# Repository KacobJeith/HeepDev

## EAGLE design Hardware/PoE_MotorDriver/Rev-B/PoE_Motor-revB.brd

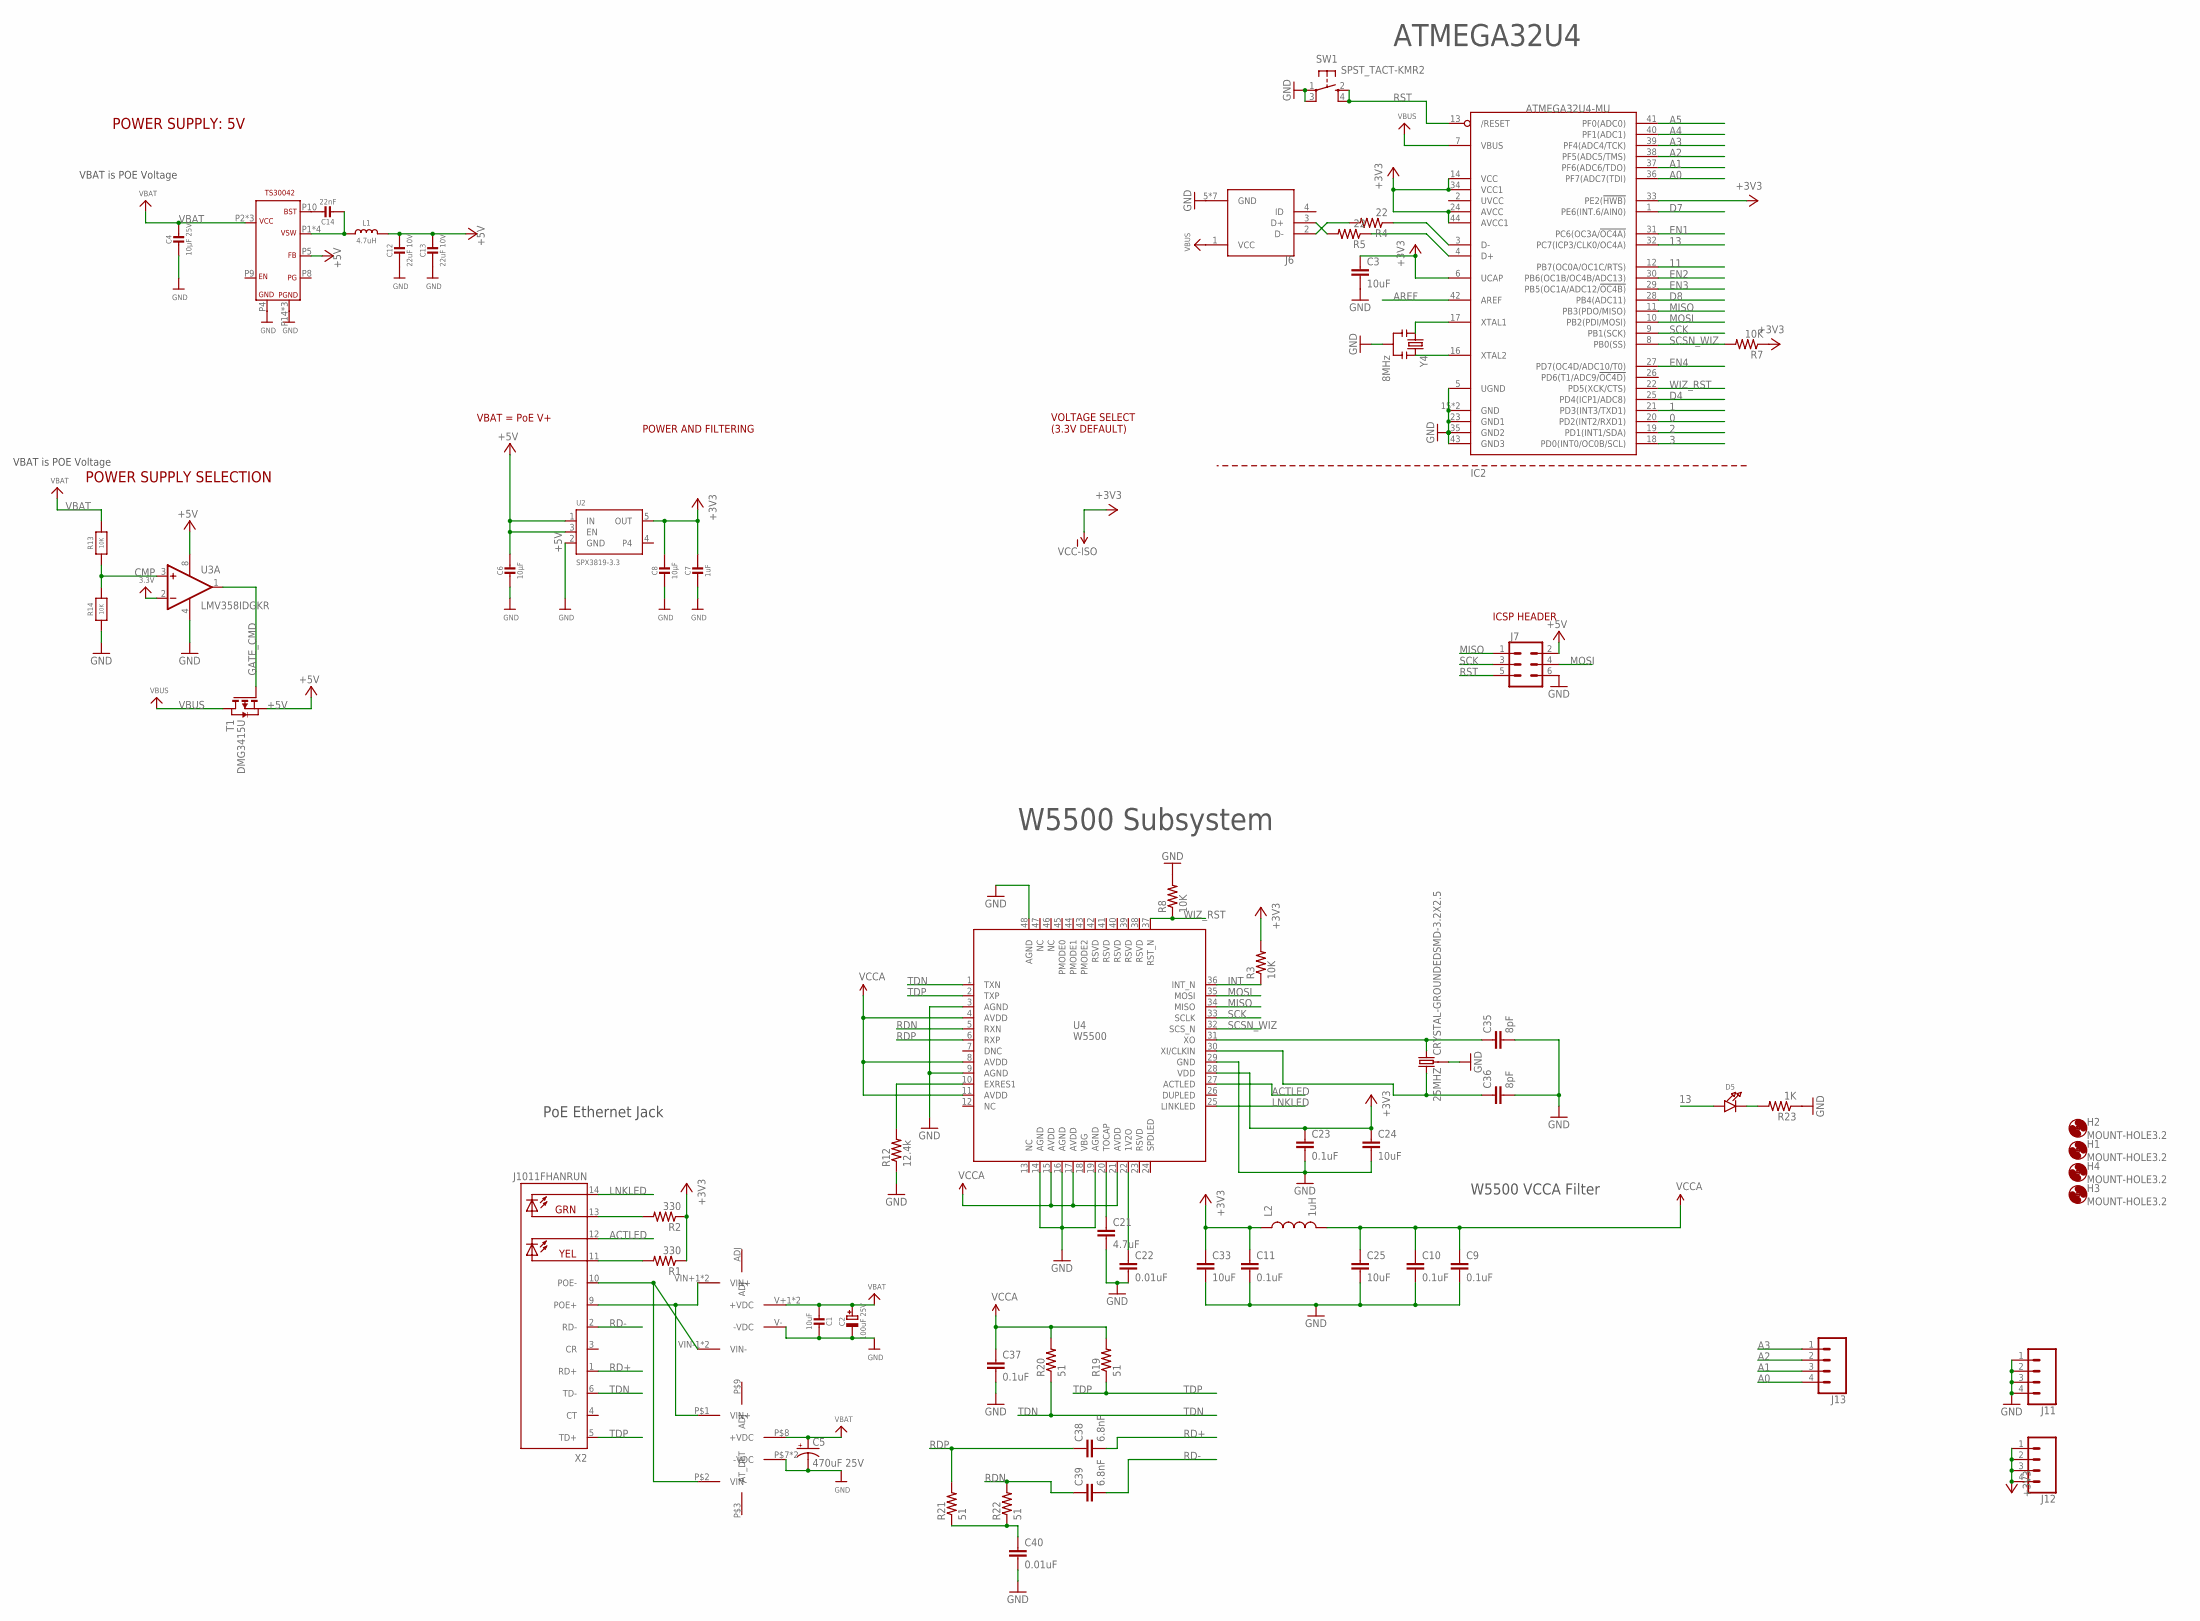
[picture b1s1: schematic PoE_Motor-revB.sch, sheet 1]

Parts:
25MHZ: CRYSTAL-GROUNDEDSMD-3.2X2.5; CRYSTAL-SMD-3.2X2.5MM
C1: 10uF; _0805MP
C2: 100uF 25V; PANASONIC_D
C3, C24, C25, C33: 10uF; 0603-CAP
C4: 10µF 25V; 0603-MINI
C5: 470uF 25V; PANASONIC_G
C6, C8: 10µF; 0603-MINI
C7: 1uF; 0603-MINI
C9, C10, C11, C23, C37: 0.1uF; 0603-CAP
C12, C13: 22uF 10V; 0603-MINI
C14: 22nF; 0603-MINI
C21: 4.7uF; 0603-CAP
C22, C40: 0.01uF; 0603-CAP
C35, C36: 8pF; 0603-CAP
C38, C39: 6.8nF; 0603-CAP
D5: LED0805_NOOUTLINE; CHIPLED_0805_NOOUTLINE
H1, H2, H3, H4: MOUNT-HOLE3.2; 3,2
IC2: ATMEGA32U4-MU; TQFN44_7MM
J6: 10103594-0001LF; FCI_10103594-0001LF
J7: CONN_03X2NO_SILK; 2X3-NS
J11, J12: CONN_04; 1X04
J13: CONN_041X04_NO_SILK; 1X04_NO_SILK
L1: 4.7uH; INDUCTOR_5X5MM_TDK_VLC5045
L2: 1uH; 0603
R1, R2: 330; 0603-RES
R3, R7, R8: 10K; 0603-RES
R4, R5: 22; 0603-RES
R12: 12.4k; 0603-RES
R13, R14: 10K; 0603-NO
R19, R20, R21, R22: 51; 0603-RES
R23: 1K; 0603-RES
SW1: SPST_TACT-KMR2; KMR2
T1: DMG3415U; SOT-23
U2: SPX3819-3.3; SOT23-5
U3: LMV358IDGKR; MSOP08
U4: W5500
U$1: SILVERTEL_POEMICRO; AG9900
U$16: AG5200AG5300; AG5300
U$19: BUCK_CONVERTER; QFN-16
X2: J1011FHANRUN; HANRUN_POE
Y4: 8MHz; RESONATOR-SMD

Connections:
0: IC2.20 (PD2(INT2/RXD1))
1: IC2.21 (PD3(INT3/TXD1))
2: IC2.19 (PD1(INT1/SDA))
3: IC2.18 (PD0(INT0/OC0B/SCL))
11: IC2.12 (PB7(OC0A/OC1C/RTS))
13: D5.A, IC2.32 (PC7(ICP3/CLK0/OC4A))
+3V3: C3.1, C7.1, C8.1, C11.1, C23.1, C24.1, C33.1, IC2.6 (UCAP), IC2.14 (VCC), IC2.24 (AVCC), IC2.33 (PE2(!HWB)), IC2.34 (VCC1), IC2.44 (AVCC1), J12.1, J12.2, J12.3, J12.4, L2.1, R1.1, R2.1, R3.2, R7.1, U2.5 (OUT), U3.2 (-IN), U4.28 (VDD)
+5V: C6.1, C12.1, C13.1, J7.2, L1.P$2 (2), T1.2 (S), U2.1 (IN), U2.3 (EN), U3.8 (V+), U$19.P5 (FB)
A0: IC2.36 (PF7(ADC7(TDI)), J13.4
A1: IC2.37 (PF6(ADC6/TDO)), J13.3
A2: IC2.38 (PF5(ADC5/TMS)), J13.2
A3: IC2.39 (PF4(ADC4/TCK)), J13.1
A4: IC2.40 (PF1(ADC1))
A5: IC2.41 (PF0(ADC0))
ACTLED: U4.27 (ACTLED), X2.12 (YEL-C)
AREF: IC2.42 (AREF)
CMP: R13.1, R14.2, U3.3 (+IN)
D4: IC2.25 (PD4(ICP1/ADC8))
D7: IC2.1 (PE6(INT.6/AIN0))
D8: IC2.28 (PB4(ADC11))
D+: IC2.4 (D+), R5.1
D-: IC2.3 (D-), R4.1
EN1: IC2.31 (PC6(OC3A/!OC4A)); also elsewhere on the board
EN2: IC2.30 (PB6(OC1B/OC4B/ADC13)); also elsewhere on the board
EN3: IC2.29 (PB5(OC1A/ADC12/!OC4B)); also elsewhere on the board
EN4: IC2.27 (PD7(OC4D/ADC10/T0)); also elsewhere on the board
GATE_CMD: T1.3 (G), U3.1 (OUT)
GND: 25MHZ.2 (3), 25MHZ.4 (3), C1.1, C2.-, C3.2, C4.2, C5.-, C6.2, C7.2, C8.2, C9.2, C10.2, C11.2, C12.2, C13.2, C21.2, C22.2, C23.2, C24.2, C25.2, C33.2, C35.2, C36.2, C37.2, C40.2, IC2.5 (UGND), IC2.15 (GND), IC2.23 (GND1), IC2.35 (GND2), IC2.43 (GND3), IC2.THERMAL (GND), J6.5 (GND), J6.P1 (GND), J6.P2 (GND), J6.P3 (GND), J6.P4 (GND), J6.P5 (GND), J6.P6 (GND), J7.6, J11.1, J11.2, J11.3, J11.4, R8.2, R12.1, R14.1, R23.1, SW1.1, SW1.3 (P1), U2.2 (GND), U3.4 (V-), U4.3 (AGND), U4.9 (AGND), U4.14 (AGND), U4.16 (AGND), U4.19 (AGND), U4.29 (GND), U4.48 (AGND), U$1.V- (-VDC), U$16.P$7 (-VDC), U$16.P$10 (-VDC), U$19.P4 (GND), U$19.P14 (PGND), U$19.P15 (PGND), U$19.PAD (PGND), Y4.2; also elsewhere on the board
INT: R3.1, U4.36 (INT_N)
LNKLED: U4.25 (LINKLED), X2.14 (GRN-C)
MISO: IC2.11 (PB3(PDO/MISO)), J7.1, U4.34 (MISO)
MOSI: IC2.10 (PB2(PDI/MOSI)), J7.4, U4.35 (MOSI)
unnamed: U$1.VIN-1 (VIN-), U$1.VIN-2 (VIN-), U$16.P$2 (VIN-), X2.10 (POE-)
unnamed: U$1.VIN+1 (VIN+), U$1.VIN+2 (VIN+), U$16.P$1 (VIN+), X2.9 (POE+)
unnamed: R2.2, X2.13 (GRN-A)
unnamed: R1.2, X2.11 (YEL-A)
unnamed: J6.3 (D+), R5.2
unnamed: D5.C, R23.2
unnamed: IC2.16 (XTAL2), Y4.3
unnamed: IC2.17 (XTAL1), Y4.1
unnamed: J6.2 (D-), R4.2
unnamed: C14.1, U$19.P10 (BST)
unnamed: C14.2, L1.P$1 (1), U$19.P1 (VSW), U$19.P12 (VSW), U$19.P13 (VSW), U$19.P16 (VSW)
unnamed: C21.1, U4.20 (TOCAP)
unnamed: C22.1, U4.22 (1V2O)
unnamed: R12.2, U4.10 (EXRES1)
unnamed: C40.1, R21.1, R22.1
unnamed: 25MHZ.3 (2), C35.1, U4.31 (XO)
unnamed: 25MHZ.1, C36.1, U4.30 (XI/CLKIN)
RD+: C38.2, X2.1 (RD+)
RD-: C39.2, X2.2 (RD-)
RDN: C39.1, R22.2, U4.5 (RXN)
RDP: C38.1, R21.2, U4.6 (RXP)
RST: IC2.13 (/RESET), J7.5, SW1.2 (S), SW1.4 (S1)
SCK: IC2.9 (PB1(SCK)), J7.3, U4.33 (SCLK)
SCSN_WIZ: IC2.8 (PB0(SS)), R7.2, U4.32 (SCS_N)
TDN: R20.1, U4.1 (TXN), X2.6 (TD-)
TDP: R19.1, U4.2 (TXP), X2.5 (TD+)
VBAT: C1.2, C2.+, C4.1, C5.+, R13.2, U$1.V+1 (+VDC), U$1.V+2 (+VDC), U$16.P$8 (+VDC), U$19.P2 (VCC), U$19.P3 (VCC), U$19.P11 (VCC); also elsewhere on the board
VBUS: IC2.7 (VBUS), J6.1 (VCC), T1.1 (D)
VCCA: C9.1, C10.1, C25.1, C37.1, L2.2, R19.2, R20.2, U4.4 (AVDD), U4.8 (AVDD), U4.11 (AVDD), U4.15 (AVDD), U4.17 (AVDD), U4.21 (AVDD)
WIZ_RST: IC2.22 (PD5(XCK/CTS)), R8.1, U4.37 (RST_N)

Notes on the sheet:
W5500 Subsystem
W5500 VCCA Filter
POWER AND FILTERING
VBAT = PoE V+
VOLTAGE SELECT (3.3V DEFAULT)
PoE Ethernet Jack
ATMEGA32U4
ICSP HEADER
POWER SUPPLY: 5V
POWER SUPPLY SELECTION
VBAT is POE Voltage

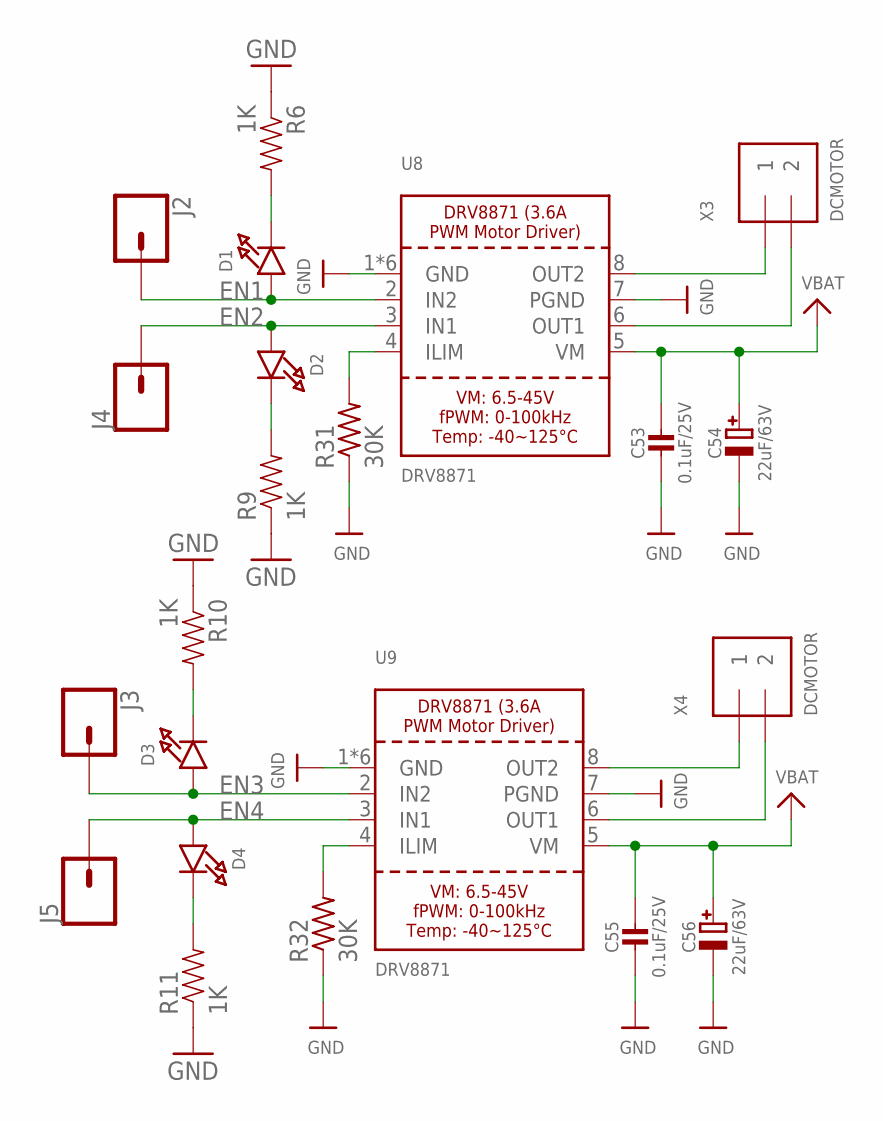
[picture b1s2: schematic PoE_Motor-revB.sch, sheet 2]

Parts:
C53, C55: 0.1uF/25V; 0603-NO
C54, C56: 22uF/63V; PANASONIC_D
D1, D2, D3, D4: LED0805_NOOUTLINE; CHIPLED_0805_NOOUTLINE
J2, J3, J4, J5: CONN_01; 1X01
R6, R9, R10, R11: 1K; 0603-RES
R31, R32: 30K; 0805-THM
U8, U9: DRV8871; HSOP8
X3, X4: DCMOTOR; TERMBLOCK_1X2-3.5MM

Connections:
EN1: D1.A, J2.1, U8.2 (IN2); also elsewhere on the board
EN2: D2.A, J4.1, U8.3 (IN1); also elsewhere on the board
EN3: D3.A, J3.1, U9.2 (IN2); also elsewhere on the board
EN4: D4.A, J5.1, U9.3 (IN1); also elsewhere on the board
GND: C53.2, C54.-, C55.2, C56.-, R6.1, R9.1, R10.1, R11.1, R31.1, R32.1, U8.1 (GND), U8.7 (PGND), U8.GND, U8.P$1 (GND), U8.P$2 (GND), U8.P$3 (GND), U8.P$4 (GND), U9.1 (GND), U9.7 (PGND), U9.GND, U9.P$1 (GND), U9.P$2 (GND), U9.P$3 (GND), U9.P$4 (GND); also elsewhere on the board
unnamed: D1.C, R6.2
unnamed: D2.C, R9.2
unnamed: D3.C, R10.2
unnamed: D4.C, R11.2
unnamed: R31.2, U8.4 (ILIM)
unnamed: R32.2, U9.4 (ILIM)
OUT1: U8.6 (OUT1), X3.2
OUT2: U8.8 (OUT2), X3.1
OUT3: U9.8 (OUT2), X4.1
OUT4: U9.6 (OUT1), X4.2
VBAT: C53.1, C54.+, C55.1, C56.+, U8.5 (VM), U9.5 (VM); also elsewhere on the board

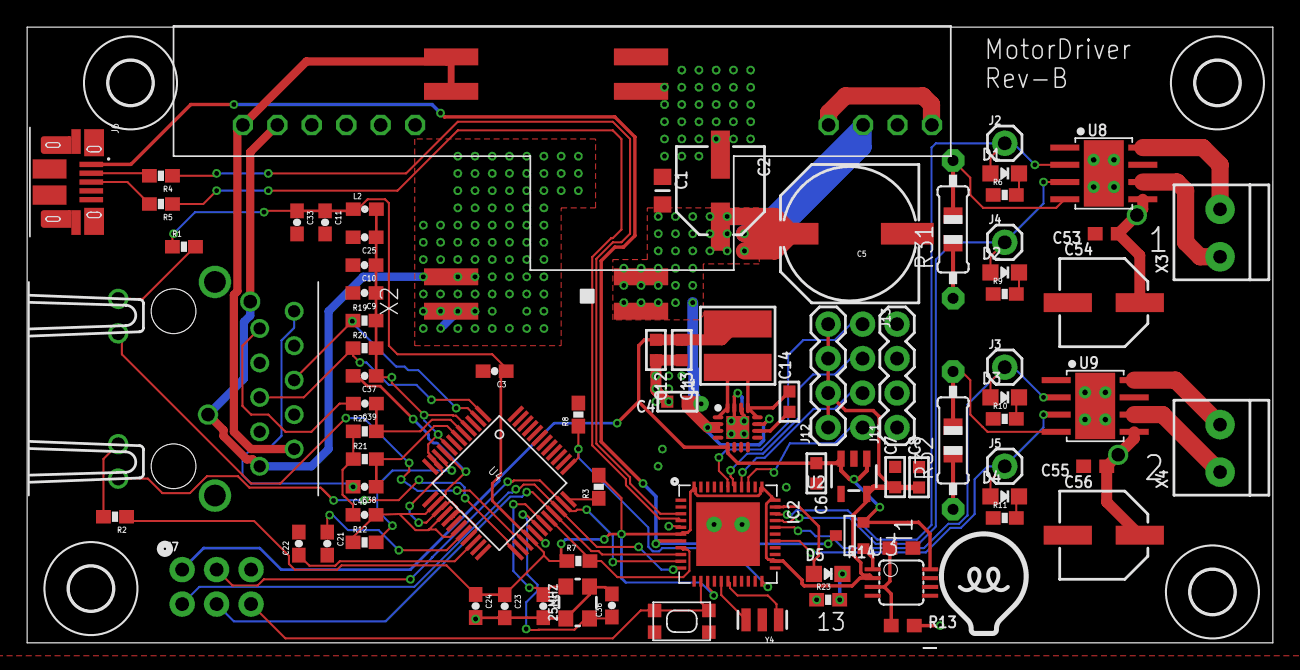
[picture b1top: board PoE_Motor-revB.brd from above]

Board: 2 copper layers, 91.8 x 45.4 mm, 88 parts (0 on the bottom side), 61 nets.

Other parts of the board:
U$15: HEEPLOGOSMALL

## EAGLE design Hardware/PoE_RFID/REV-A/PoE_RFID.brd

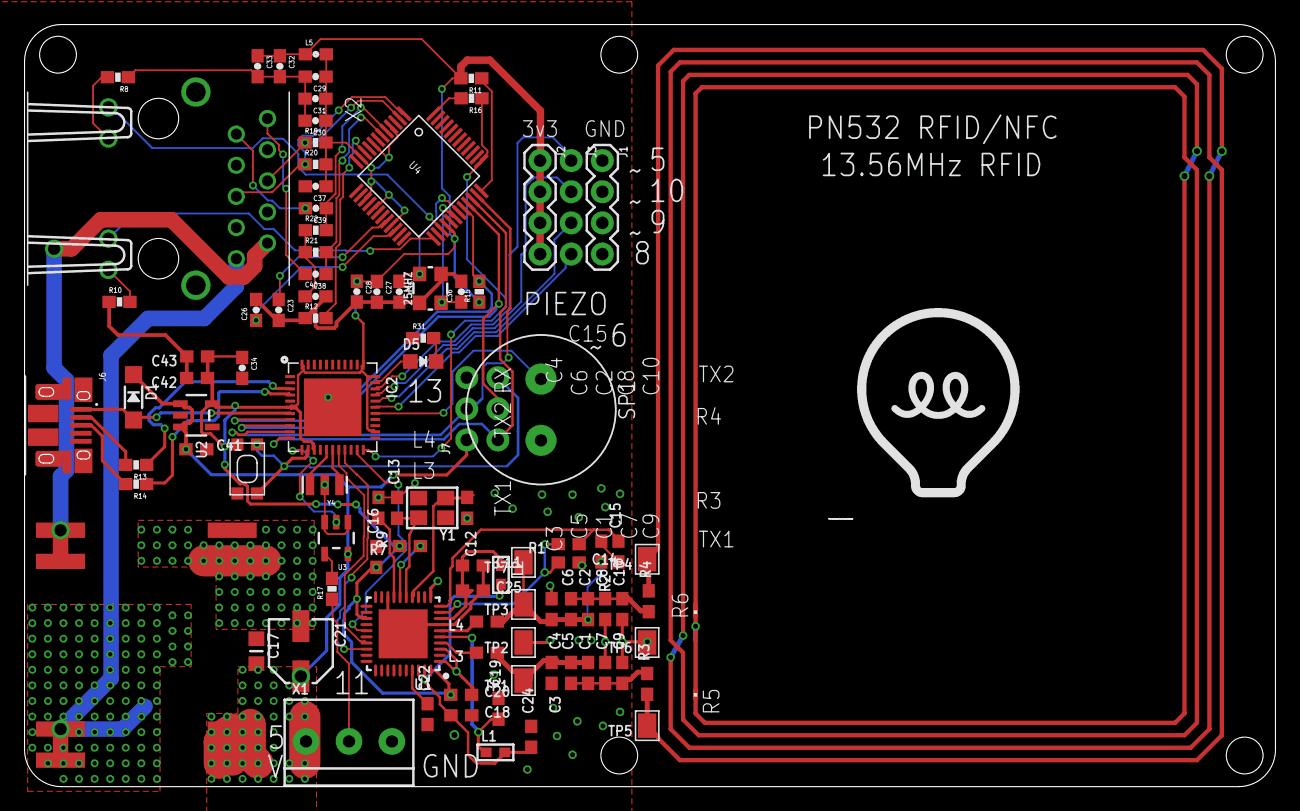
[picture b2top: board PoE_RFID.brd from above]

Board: 2 copper layers, 102.0 x 62.1 mm, 98 parts (0 on the bottom side), 68 nets.

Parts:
25MHZ: CRYSTAL-GROUNDEDSMD-3.2X2.5; CRYSTAL-SMD-3.2X2.5MM
C1, C2, C12, C13: 22pF; 0603-NO
C3, C4: 220pF; 0603-NO
C5, C6, C9, C10: NC; 0603-NO
C7, C8: 100pF; 0603-NO
C11, C14, C16, C20, C24: 0.1µF; 0603-NO
C15: 1000pF; 0603-NO
C17: 10uF; _0805MP
C18, C19, C22, C25, C41, C43: 10µF; 0603-NO
C21: 100uF; PANASONIC_C
C23: 4.7uF; 0603-CAP
C26, C40: 0.01uF; 0603-CAP
C27, C30, C31, C32, C37: 0.1uF; 0603-CAP
C28, C29, C33, C34: 10uF; 0603-CAP
C35, C36: 8pF; 0603-CAP
C38, C39: 6.8nF; 0603-CAP
C42: 1uF; 0603-NO
D1: SOD-123
D5: CHIPLED_0805_NOOUTLINE
IC2: ATMEGA32U4-MU; TQFN44_7MM
J1, J2: 1X04
J3: 1X04_NO_SILK
J6: 10103594-0001LF; FCI_10103594-0001LF
J7: 2X3-NS
L1, L2: FERRITE; _0603
L3, L4: 560nH; 0603-NO
L5: 1uH; 0603
R1: 1.0K; 0603-NO
R2: 1.69K; 0603-NO
R3, R4: 1.5; 0603-NO
R5, R6: NC; R0201
R7, R9: 10K; 0603-NO
R8, R10: 330; 0603-RES
R11, R15, R16: 10K; 0603-RES
R12: 12.4k; 0603-RES
R13, R14: 22; 0603-RES
R17: 100; 0603-RES
R19, R20, R21, R22: 51; 0603-RES
R31: 1K; 0603-RES
SP1: SPEAKER/PS12; PS12
SW1: SPST_TACT-KMR2; KMR2
TP1: TX1_POST; PAD-1.5X2.0
TP2, TP6: TGND; PAD-1.5X2.0
TP3: TX2_POST; PAD-1.5X2.0
TP4: TX2_PRE; PAD-1.5X2.0
TP5: TX1_PRE; PAD-1.5X2.0
TP7: RX; PAD-1.5X2.0
U1: PN532; HVQFN40-6X6
U2: SPX3819-3.3; SOT23-5
U3: 74AHC1G125; SOT23-5
U4: W5500
U$1: SILVERTEL_POEMICRO; AG9900
U$19: HEEPLOGO
X1: TERMBLOCK_1X3-3.5MM
X2: J1011FHANRUN; HANRUN_POE
Y1: 27.12MHz; CRYSTAL_3.2X2.5
Y4: 8MHz; RESONATOR-SMD

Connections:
5_PWM: IC2.31, J3.1
9_PWM: IC2.29, J3.3
10_PWM: IC2.30, J3.2
13: D5.A, IC2.32
+3V3: C16.1, C20.1, C27.1, C28.1, C32.1, C33.1, C34.1, C42.1, C43.1, IC2.6, IC2.14, IC2.24, IC2.33, IC2.34, IC2.44, J2.1, J2.2, J2.3, J2.4, L5.1, R7.2, R11.2, R15.1, U1.23, U1.40, U2.5, U4.28
+5V: C17.2, C21.+, C41.1, D1.C, J7.2, U2.1, U2.3, U3.5, U$1.V+1, U$1.V+2, X1.3
ACTLED: U4.27, X2.11
D8: IC2.28, J3.4
D+: IC2.4, R14.1
D-: IC2.3, R13.1
EN3: IC2.27, SP1.P$1
GND: 25MHZ.2, 25MHZ.4, C3.2, C4.1, C7.2, C8.1, C9.2, C10.1, C11.2, C12.2, C13.2, C14.2, C16.2, C17.1, C18.2, C19.2, C20.2, C21.-, C22.1, C23.2, C24.2, C25.2, C26.2, C27.2, C28.2, C29.2, C30.2, C31.2, C32.2, C33.2, C34.2, C35.2, C36.2, C37.2, C40.2, C41.2, C42.2, C43.2, IC2.5, IC2.15, IC2.23, IC2.35, IC2.43, IC2.THERMAL, J1.1, J1.2, J1.3, J1.4, J6.5, J6.P1, J6.P2, J6.P3, J6.P4, J6.P5, J6.P6, J7.6, R5.2, R6.1, R8.1, R9.1, R10.1, R12.1, R16.2, R31.1, SP1.P$2, SW1.1, SW1.3, TP2.P$1, TP6.P$1, U1.1, U1.3, U1.7, U1.11, U1.18, U1.TP, U2.2, U3.1, U3.3, U4.3, U4.9, U4.14, U4.16, U4.19, U4.29, U4.48, U$1.V-, X1.1, Y4.2
INT: R11.1, U4.36
IRQ: IC2.21, U1.25
LNKLED: U4.25, X2.13
MISO: IC2.11, J7.1, U4.34
MOSI: IC2.10, J7.4, U4.35
MOSI/SDA/TX: IC2.19, U1.28
unnamed: L3.2, U1.4
unnamed: L4.2, U1.6
unnamed: C1.2, C3.1, C5.2, L3.1, TP1.P$1
unnamed: R3.1, R6.2, TP5.P$1
unnamed: R4.2, R5.1, TP4.P$1
unnamed: U$1.VIN-1, U$1.VIN-2, X2.10
unnamed: C12.1, U1.14, Y1.1
unnamed: C13.1, U1.15, Y1.2
unnamed: C15.1, R2.1
unnamed: C14.1, R1.2, U1.9
unnamed: C15.2, R1.1, U1.10
unnamed: C2.1, C4.2, C6.1, L4.1, R2.2, TP3.P$1, TP7.P$1
unnamed: C11.1, C25.1, L2.1, U1.8
unnamed: C19.1, L1.1, U1.5
unnamed: U$1.VIN+1, U$1.VIN+2, X2.9
unnamed: C26.1, U4.22
unnamed: IC2.16, Y4.3
unnamed: C23.1, U4.20
unnamed: R17.2, U3.4
unnamed: R12.2, U4.10
unnamed: IC2.17, Y4.1
unnamed: J6.3, R14.2
unnamed: C40.1, R21.1, R22.1
unnamed: J6.2, R13.2
unnamed: 25MHZ.3, C35.1, U4.31
unnamed: 25MHZ.1, C36.1, U4.30
unnamed: R10.2, X2.14
unnamed: R8.2, X2.12
unnamed: D5.C, R31.2
unnamed: C22.2, U1.37
NEO_3V: IC2.12, U3.2
NEO_5V: R17.1, X1.2
NSS/SCL/RX: IC2.18, U1.27
RD+: C38.2, X2.1
RD-: C39.2, X2.2
RDN: C39.1, R22.2, U4.5
RDP: C38.1, R21.2, U4.6
RST: IC2.13, J7.5, SW1.2, SW1.4
SCK: IC2.9, J7.3, U4.33
SCSN_WIZ: IC2.8, R15.2, U4.32
SEL0: R7.1, U1.16
SEL1: R9.2, U1.17
TDN: R20.1, U4.1, X2.6
TDP: R19.1, U4.2, X2.5
TX1_ANTENNA: C1.1, C5.1, C7.1, C9.1, R3.2
TX2_ANTENNA: C2.2, C6.2, C8.2, C10.2, R4.1
VBUS: D1.A, IC2.7, J6.1
VCC: C18.1, C24.1, L1.2, L2.2, U1.39
VCCA: C29.1, C30.1, C31.1, C37.1, L5.2, R19.2, R20.2, U4.4, U4.8, U4.11, U4.15, U4.17, U4.21
WIZ_RST: IC2.22, R16.1, U4.37

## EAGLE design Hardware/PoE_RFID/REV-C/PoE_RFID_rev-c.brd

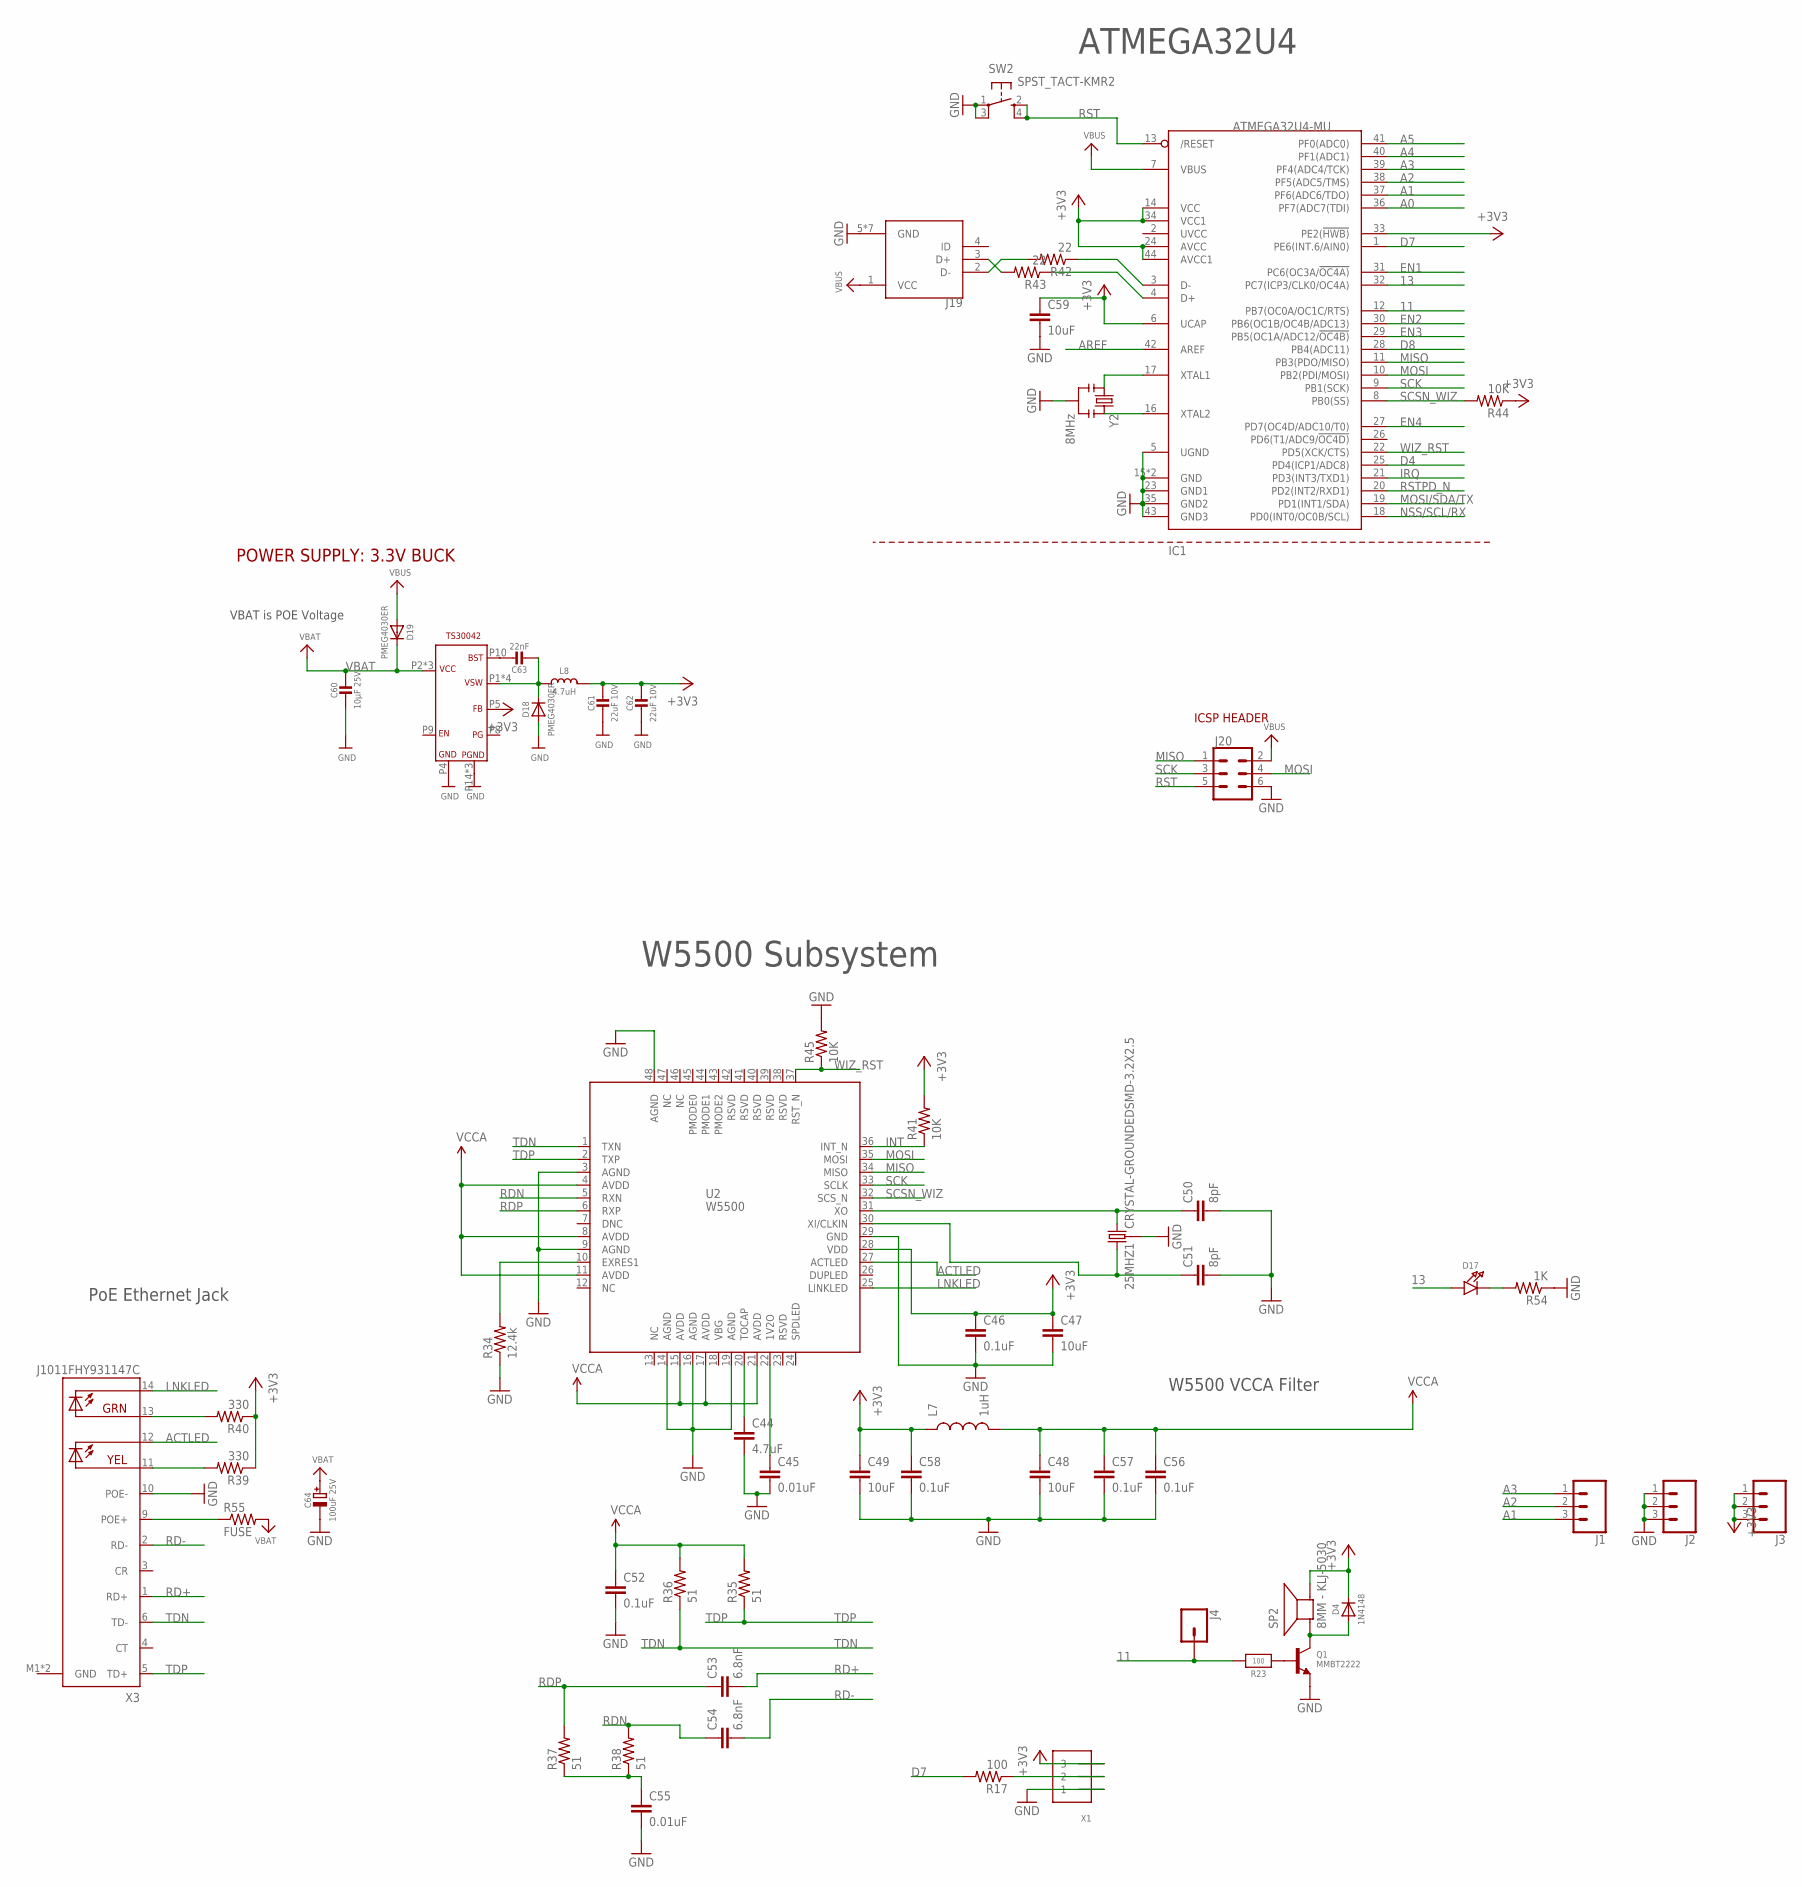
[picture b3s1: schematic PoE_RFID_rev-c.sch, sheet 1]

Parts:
25MHZ1: CRYSTAL-GROUNDEDSMD-3.2X2.5; CRYSTAL-SMD-3.2X2.5MM
C44: 4.7uF; 0603-CAP
C45, C55: 0.01uF; 0603-CAP
C46, C52, C56, C57, C58: 0.1uF; 0603-CAP
C47, C48, C49, C59: 10uF; 0603-CAP
C50, C51: 8pF; 0603-CAP
C53, C54: 6.8nF; 0603-CAP
C60: 10µF 25V; 0603-MINI
C61, C62: 22uF 10V; 0603-MINI
C63: 22nF; 0603-MINI
C64: 100uF 25V; PANASONIC_D
D4: 1N4148; SOD-323
D17: LED0805_NOOUTLINE; CHIPLED_0805_NOOUTLINE
D18, D19: PMEG4030ER; SOD-123
IC1: ATMEGA32U4-MU; TQFN44_7MM
J1: CONN_031X03_NO_SILK; 1X03_NO_SILK
J2, J3: CONN_03; 1X03
J4: CONN_01; 1X01
J19: 10103594-0001LF; FCI_10103594-0001LF
J20: CONN_03X2NO_SILK; 2X3-NS
L7: 1uH; 0603
L8: 4.7uH; INDUCTOR_5X5MM_TDK_VLC5045
Q1: MMBT2222; SOT23-WIDE
R17: 100; 0603-RES
R23: 100; 0603-NO@1
R34: 12.4k; 0603-RES
R35, R36, R37, R38: 51; 0603-RES
R39, R40: 330; 0603-RES
R41, R44, R45: 10K; 0603-RES
R42, R43: 22; 0603-RES
R54: 1K; 0603-RES
R55: FUSE; 0603-RES
SP2: 8MM - KLJ-5030; BUZZER_SMT_5MM
SW2: SPST_TACT-KMR2; KMR2
U2: W5500
U$55: BUCK_CONVERTER; QFN-16
X1: TERMBLOCK_1X3; TERMBLOCK_1X3-3.5MM
X3: J1011FHY931147C; HANRUN_POE
Y2: 8MHz; RESONATOR-SMD

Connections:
11: IC1.12 (PB7(OC0A/OC1C/RTS)), J4.1, R23.2
13: D17.A, IC1.32 (PC7(ICP3/CLK0/OC4A))
+3V3: C46.1, C47.1, C49.1, C58.1, C59.1, C61.1, C62.1, D4.C, IC1.6 (UCAP), IC1.14 (VCC), IC1.24 (AVCC), IC1.33 (PE2(!HWB)), IC1.34 (VCC1), IC1.44 (AVCC1), J3.1, J3.2, J3.3, L7.1, L8.P$2 (2), R39.1, R40.1, R41.2, R44.1, SP2.-, U2.28 (VDD), U$55.P5 (FB), X1.3; also elsewhere on the board
A0: IC1.36 (PF7(ADC7(TDI))
A1: IC1.37 (PF6(ADC6/TDO)), J1.3
A2: IC1.38 (PF5(ADC5/TMS)), J1.2
A3: IC1.39 (PF4(ADC4/TCK)), J1.1
A4: IC1.40 (PF1(ADC1))
A5: IC1.41 (PF0(ADC0))
ACTLED: U2.27 (ACTLED), X3.12 (YEL-C)
AREF: IC1.42 (AREF)
D4: IC1.25 (PD4(ICP1/ADC8))
D7: IC1.1 (PE6(INT.6/AIN0)), R17.2
D8: IC1.28 (PB4(ADC11))
D+1: IC1.4 (D+), R43.1
D-1: IC1.3 (D-), R42.1
EN1: IC1.31 (PC6(OC3A/!OC4A))
EN2: IC1.30 (PB6(OC1B/OC4B/ADC13))
EN3: IC1.29 (PB5(OC1A/ADC12/!OC4B))
EN4: IC1.27 (PD7(OC4D/ADC10/T0))
GND: 25MHZ1.2 (3), 25MHZ1.4 (3), C44.2, C45.2, C46.2, C47.2, C48.2, C49.2, C50.2, C51.2, C52.2, C55.2, C56.2, C57.2, C58.2, C59.2, C60.2, C61.2, C62.2, C64.-, D18.A, IC1.5 (UGND), IC1.15 (GND), IC1.23 (GND1), IC1.35 (GND2), IC1.43 (GND3), IC1.THERMAL (GND), J2.1, J2.2, J2.3, J19.5 (GND), J19.P1 (GND), J19.P2 (GND), J19.P3 (GND), J19.P4 (GND), J19.P5 (GND), J19.P6 (GND), J20.6, Q1.2 (E), R34.1, R45.2, R54.1, SW2.1, SW2.3 (P1), U2.3 (AGND), U2.9 (AGND), U2.14 (AGND), U2.16 (AGND), U2.19 (AGND), U2.29 (GND), U2.48 (AGND), U$55.P4 (GND), U$55.P14 (PGND), U$55.P15 (PGND), U$55.PAD (PGND), X1.1, X3.10 (POE-), X3.M1 (GND), X3.M2 (GND), Y2.2; also elsewhere on the board
INT: R41.1, U2.36 (INT_N)
IRQ: IC1.21 (PD3(INT3/TXD1)); also elsewhere on the board
LNKLED: U2.25 (LINKLED), X3.14 (GRN-C)
MISO: IC1.11 (PB3(PDO/MISO)), J20.1, U2.34 (MISO)
MOSI: IC1.10 (PB2(PDI/MOSI)), J20.4, U2.35 (MOSI)
MOSI/SDA/TX: IC1.19 (PD1(INT1/SDA)); also elsewhere on the board
unnamed: R17.1, X1.2
unnamed: Q1.1 (B), R23.1
unnamed: D4.A, Q1.3 (C), SP2.+
unnamed: C44.1, U2.20 (TOCAP)
unnamed: C45.1, U2.22 (1V2O)
unnamed: R34.2, U2.10 (EXRES1)
unnamed: C55.1, R37.1, R38.1
unnamed: 25MHZ1.3 (2), C50.1, U2.31 (XO)
unnamed: 25MHZ1.1, C51.1, U2.30 (XI/CLKIN)
unnamed: IC1.16 (XTAL2), Y2.3
unnamed: IC1.17 (XTAL1), Y2.1
unnamed: J19.3 (D+), R43.2
unnamed: J19.2 (D-), R42.2
unnamed: D17.C, R54.2
unnamed: R40.2, X3.13 (GRN-A)
unnamed: R39.2, X3.11 (YEL-A)
unnamed: C63.1, U$55.P10 (BST)
unnamed: C63.2, D18.C, L8.P$1 (1), U$55.P1 (VSW), U$55.P12 (VSW), U$55.P13 (VSW), U$55.P16 (VSW)
unnamed: R55.1, X3.9 (POE+)
NSS/SCL/RX: IC1.18 (PD0(INT0/OC0B/SCL)); also elsewhere on the board
RD+: C53.2, X3.1 (RD+)
RD-: C54.2, X3.2 (RD-)
RDN: C54.1, R38.2, U2.5 (RXN)
RDP: C53.1, R37.2, U2.6 (RXP)
RST: IC1.13 (/RESET), J20.5, SW2.2 (S), SW2.4 (S1)
RSTPD_N: IC1.20 (PD2(INT2/RXD1)); also elsewhere on the board
SCK: IC1.9 (PB1(SCK)), J20.3, U2.33 (SCLK)
SCSN_WIZ: IC1.8 (PB0(SS)), R44.2, U2.32 (SCS_N)
TDN: R36.1, U2.1 (TXN), X3.6 (TD-)
TDP: R35.1, U2.2 (TXP), X3.5 (TD+)
VBAT: C60.1, C64.+, D19.C, R55.2, U$55.P2 (VCC), U$55.P3 (VCC), U$55.P11 (VCC)
VBUS: D19.A, IC1.7 (VBUS), J19.1 (VCC), J20.2
VCCA: C48.1, C52.1, C56.1, C57.1, L7.2, R35.2, R36.2, U2.4 (AVDD), U2.8 (AVDD), U2.11 (AVDD), U2.15 (AVDD), U2.17 (AVDD), U2.21 (AVDD)
WIZ_RST: IC1.22 (PD5(XCK/CTS)), R45.1, U2.37 (RST_N)

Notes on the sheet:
W5500 Subsystem
W5500 VCCA Filter
PoE Ethernet Jack
ATMEGA32U4
ICSP HEADER
POWER SUPPLY: 3.3V BUCK
VBAT is POE Voltage

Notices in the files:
parts and their libraries:
microbuilder: This work is placed in the public domain, and may be freely used for commercial and non-commercial work with the following conditions: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
SparkFun-Clocks: Licensing: Creative Commons ShareAlike 4.0 International - https://creativecommons.org/licenses/by-sa/4.0
